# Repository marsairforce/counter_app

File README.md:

# A simple counter application

This is a device that has 2 7-segment displays, and buttons.

It can be used for simple manual counting of something.
I originally built it for a "It has been xx days since.." signs.

But it can also be used for one of those "Now serving xx" signs.

This project was a test of the waters to see what OSHPark is able to create.

It started off as a breadboard experiment, then a hand wire job on a punchboard, and then a finished PCB board.

It was an exercise to learn how to use Kicad as well. Before I had been trying to use gEDA and suite to make a circuit board layout, but never got past the schematic phase. Perhaps because there is no existing parts or footprint library for gEDA and also no documentation for how to use the tools (that are not even GUI based) to try to create a symbol and a footprint.  I was able to get farther with Kicad in an evening than I was able to get over several years of coming back to poking at gEDA.

It was also the first product built using Attiny-85 device. Learning how to use shift registers, multiplex switch button inputs, software interrupts.

All the components were things I had in stock, thru-hole parts.

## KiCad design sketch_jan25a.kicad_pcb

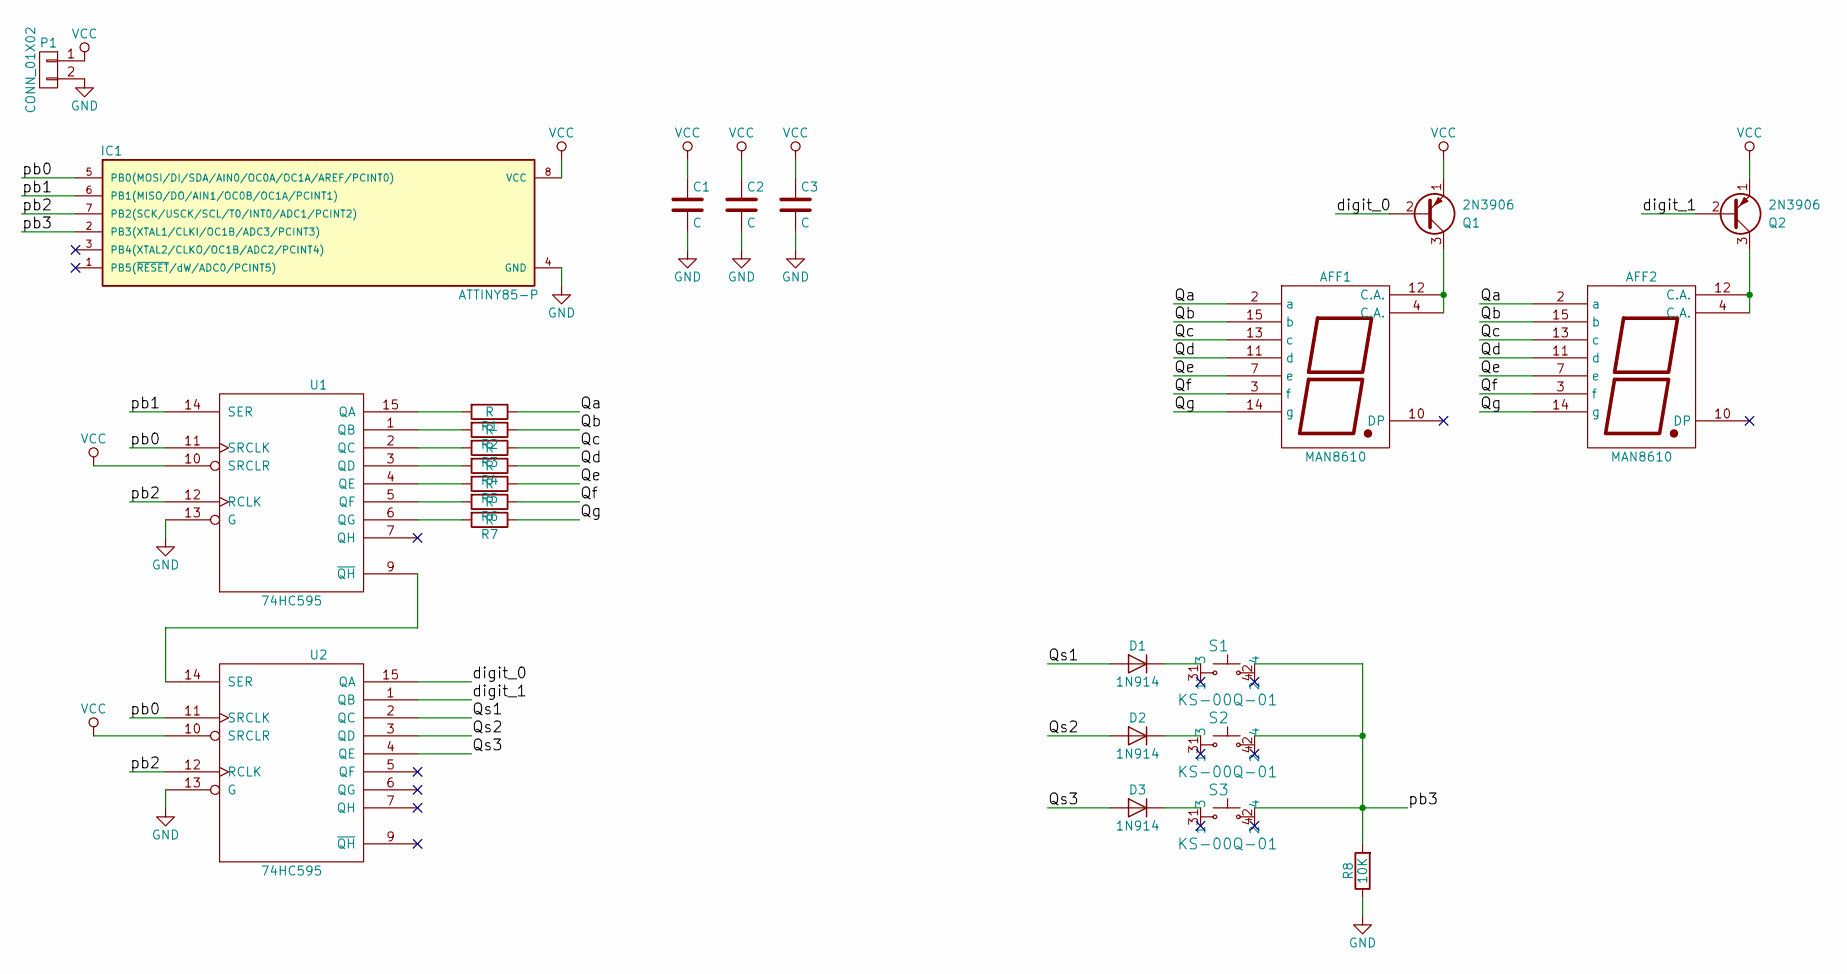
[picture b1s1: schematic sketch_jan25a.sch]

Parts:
AFF1, AFF2: MAN8610
C1, C2, C3: C; C_Rect_L7_W2.5_P5
D1, D2, D3: 1N914; Diode_DO-35_SOD27_Horizontal_RM10
IC1: ATTINY85-P; DIP-8_W7.62mm
P1: CONN_01X02
Q1, Q2: 2N3906; TO-92_Inline_Narrow_Oval
R1, R2, R3, R4, R5, R6, R7: R; Resistor_Vertical_RM5mm
R8: 10K; Resistor_Vertical_RM5mm
S1, S2, S3: KS-00Q-01; e_switch
U1, U2: 74HC595; DIP-16_W7.62mm

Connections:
/Qa: AFF1.2 (a), AFF2.2 (a), R1.1
/Qb: AFF1.15 (b), AFF2.15 (b), R2.1
/Qc: AFF1.13 (c), AFF2.13 (c), R3.1
/Qd: AFF1.11 (d), AFF2.11 (d), R4.1
/Qe: AFF1.7 (e), AFF2.7 (e), R5.1
/Qf: AFF1.3 (f), AFF2.3 (f), R6.1
/Qg: AFF1.14 (g), AFF2.14 (g), R7.1
/Qs1: D1.2 (A), U2.2 (QC)
/Qs2: D2.2 (A), U2.3 (QD)
/Qs3: D3.2 (A), U2.4 (QE)
/digit_0: Q1.2 (B), U2.15 (QA)
/digit_1: Q2.2 (B), U2.1 (QB)
/pb0: IC1.5 (PB0(MOSI/DI/SDA/AIN0/OC0A/OC1A/AREF/PCI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), U1.11 (SRCLK), U2.11 (SRCLK)
/pb1: IC1.6 (PB1(MISO/DO/AIN1/OC0B/OC1A/PCINT1)), U1.14 (SER)
/pb2: IC1.7 (PB2(SCK/USCK/SCL/T0/INT0/ADC1/PCINT2)), U1.12 (RCLK), U2.12 (RCLK)
/pb3: IC1.2 (PB3(XTAL1/CLKI/OC1B/ADC3/PCINT3)), R8.2, S1.2, S2.2, S3.2
GND: C1.2, C2.2, C3.2, IC1.4 (GND), P1.2, R8.1, U1.8 (GND), U1.13 (G), U2.8 (GND), U2.13 (G)
unnamed: AFF1.4 (C.A.), AFF1.12 (C.A.), Q1.3 (C)
unnamed: AFF2.4 (C.A.), AFF2.12 (C.A.), Q2.3 (C)
unnamed: D1.1 (K), S1.1
unnamed: D2.1 (K), S2.1
unnamed: D3.1 (K), S3.1
unnamed: R1.2, U1.15 (QA)
unnamed: R2.2, U1.1 (QB)
unnamed: R3.2, U1.2 (QC)
unnamed: R4.2, U1.3 (QD)
unnamed: R5.2, U1.4 (QE)
unnamed: R6.2, U1.5 (QF)
unnamed: R7.2, U1.6 (QG)
unnamed: U1.9 (~QH), U2.14 (SER)
VCC: C1.1, C2.1, C3.1, IC1.8 (VCC), P1.1, Q1.1 (E), Q2.1 (E), U1.10 (SRCLR), U1.16 (VCC), U2.10 (SRCLR), U2.16 (VCC)

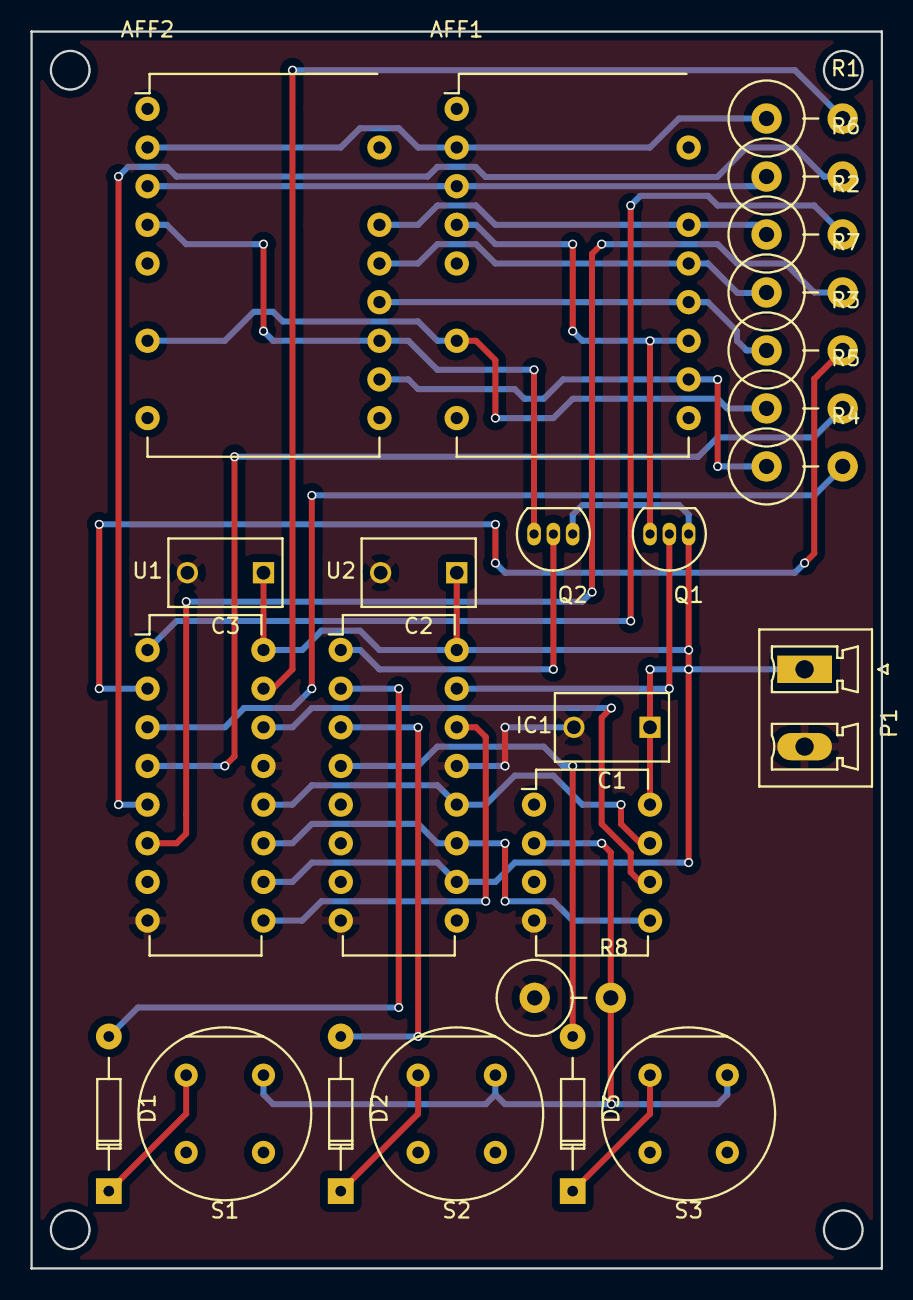
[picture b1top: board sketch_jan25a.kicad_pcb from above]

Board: 2 copper layers, 55.9 x 81.3 mm, 25 parts (0 on the bottom side), 31 nets.

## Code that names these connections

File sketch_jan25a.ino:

/*
 * The "It has ben XX days since .. Application.
 * 
 * Two displays. Three buttons. To control the value displayed.
 * 
 * Where we drive the cathodes with one 74595 and the anodes (through a transistor driver) with another 74595.
 * Using the extra pins on the 2nd 74595 to drive up to 6 switch inputs.
 * 
 * Trying to get this onto ATtiny85
 * 
 * PB2 (7) - RCLK (12)
 * PB1 (6) - SER (14)
 * PB0 (5) - SRCLK (11)
 * PB3 (2) - switch input
 * 
 * Where the 74595(1) is connected to the 7 segment display as
 * Q0 - Ca
 * Q1 - Cb
 * Q2 - Cc
 * Q3 - Cd
 * Q4 - Ce
 * Q5 - Cf
 * Q6 - Cg
 * Q7 - Cdp
 * 
 * And the 74595(2) is connected to the transistor drivers.
 * Q0 - 1's digit
 * Q1 - 10's digit
 * Q2 - S0 - reset
 * Q3 - S1 - increment
 */

// these are bit positions for shifting, instead of using digital write
// so we can do PORTB |= (1<<pin) to set
// and PORTB &= ~(1<<pin) to clear
// Since this saves us 4 microseconds per operation.

#define sbi(port,bit) \
  (port) |= (1 << (bit)) 

#define cbi(port,bit) \
  (port) &= ~(1 << (bit)) 
  
#include <avr/interrupt.h>

const int clockPin = 0; // PB0 connected to SRCLK on 74595
const int dataPin = 1; // PB1 connected to SER on 74595
const int latchPin = 2; // conected to RCLK on 74595
const int inputPin = 3; // connected to pushbutton switches after 2nd 74595
// 4
// 5 - requires a high voltage programmer to reprogram device is we remove reset function?

// display 0,1,2,3,4,5,6,7,8,9, MSB shifted first (LSB is a segment)
int datArray[10] = { 0xC0, 0xF9, 0xA4, 0xB0, 0x99, 0x92, 0x82, 0xF8, 0x80, 0x90 };
// LSB shifted first
//int datArray[10]= { 0x03, 0x9F, 0x25, 0x0D, 0x99, 0x49, 0x41, 0x1F, 0x01, 0x09 };

const int maxDigits = 2;

// the digit to display
int digitMap[maxDigits] = { 0x02, 0x01 }; // pnp transistors, so these are active low now.

// we basically use unpacked BCD
// [0] - one's digit
// [1] - ten's digit
int displayValue[maxDigits];


// causes one digit to be written to the 7 segment display
// value: the index to the digitArray to display.
// digit: a value from 0-7
void writeDigit(int value, int digit) {
  
    PORTB &= ~(1<<latchPin);// ground latch pin and hold low as long as we are transmitting data.

    // the switches are "after" the display driver, so the need to be shifted first.
    // practically we combine the switch bitmap with the active display digit map, writing a 1 to the enabled switches
    // which is currently the lower 6 bits. 0x2F
    int  control = digitMap[digit]|0xFC;
    // because we have the anode and transistor driver wired after the cathode driver, we have to shift it out first.
    shiftOut(dataPin, clockPin, MSBFIRST, control);

    
    // we used to need to drive out LSB first, because we have Q0 connected to Ca, which is last
    // but reversed our bitmap abover to support MSB first. Either that or we could rewire the display.
    shiftOut(dataPin, clockPin, MSBFIRST, datArray[value]);  
    
    //digitalWrite(latchPin, HIGH);
    PORTB |= (1<<latchPin);
}

void resetDigits() {
  for (int i = 0; i < maxDigits; i++) {
    displayValue[i] = 0;
  }
}

volatile boolean checking_input = false;

void writeDigits() {
  if (checking_input) {
    // do not try to update display if we are trying to read an input.
    return;
  }
  for (int n = 0; n < maxDigits; n++) {
  
    writeDigit(displayValue[n], n);
   // delay(4);
  }
}

void increment() {
  for (int i = 0; i < maxDigits; i++) {
    displayValue[i] ++;
    if (displayValue[i] > 9) {
      displayValue[i] = 0;
      if (i + 1 < maxDigits) {
        continue;
      }
    }
    else {
      break;
    }
  } // for
}

void decrement() {
  int borrow = false;
  // do the ten's compliment of each digit
  for (int i = 0; i < maxDigits; i++) {
    int compliment=0;
    if (borrow) {
      10-displayValue[i];
    }
    else {
      compliment=10-1;
    }
    int result = (displayValue[i] + compliment);
    if (result >=10) {
      borrow = true;
    }
    displayValue[i] = result % 10;
  } // for
}

void setup() {     
  
  // put your setup code here, to run once:
  pinMode(latchPin, OUTPUT);
  pinMode(clockPin, OUTPUT);
  pinMode(dataPin, OUTPUT);
  pinMode(inputPin, INPUT);
  
  resetDigits();

  cli();
  GIMSK |= (1 << PCIE); // enable pin change interrupts
  //sbi(PCMSK, PCINT3);
  PCMSK |= (1 << PCINT3);
  sei();

}

// inspired by Arduino inputs from 74595 http://www.kevindarrah.com/download/arduino_code/ShiftRegisterInput2_piano.ino
//void pin_read(){
ISR(PCINT0_vect) {

  if (GIFR & (1 << PCIF) == 0) {
    return; // not a pin change interrupt
  }
    // switch debouncing logic
    for(int j=0; j<50; j++) {
      delayMicroseconds(1000);
    }
    
    if (digitalRead(inputPin) == LOW) {
      return;
    }

  checking_input = true;
   
    // determine which button(s) are presesed
    // shift out the bitmap that represents the 1st button
    PORTB &= ~(1<<latchPin);
    shiftOut(dataPin, clockPin, MSBFIRST, 0x07); // 0x04 for the switch, + 0x03 to cause displays to blank.
    shiftOut(dataPin, clockPin, MSBFIRST, 0x00);
    PORTB |= (1<<latchPin);
    if (digitalRead(inputPin) == HIGH) {
      resetDigits();
      goto done;
    }

    // shift out the bitmap that represents the 2nd button
    PORTB &= ~(1<<latchPin);
    shiftOut(dataPin, clockPin, MSBFIRST, 0x0B); // 0x08 for the switch, + 0x03 to cause displays to blank.
    shiftOut(dataPin, clockPin, MSBFIRST, 0x00);
    PORTB |= (1<<latchPin);
    if (digitalRead(inputPin) == HIGH) {
      decrement();
      goto done;
    }

    // shift out the bitmap that represents the 3rd button
    PORTB &= ~(1<<latchPin);
    shiftOut(dataPin, clockPin, MSBFIRST, 0x13); // 0x10 for the switch, + 0x03 to cause displays to blank.
    shiftOut(dataPin, clockPin, MSBFIRST, 0x00);
    PORTB |= (1<<latchPin);
    if (digitalRead(inputPin) == HIGH) {
      increment();
      goto done;
    }


done:
    // keep us here until button is released.
    while(digitalRead(inputPin) == HIGH){ 
      delayMicroseconds(1000); 
    }

  checking_input = false;
}//pin_read


void loop() {
  writeDigits();
}

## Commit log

2018-02-05 migrate project from arduino workspace to its own module
